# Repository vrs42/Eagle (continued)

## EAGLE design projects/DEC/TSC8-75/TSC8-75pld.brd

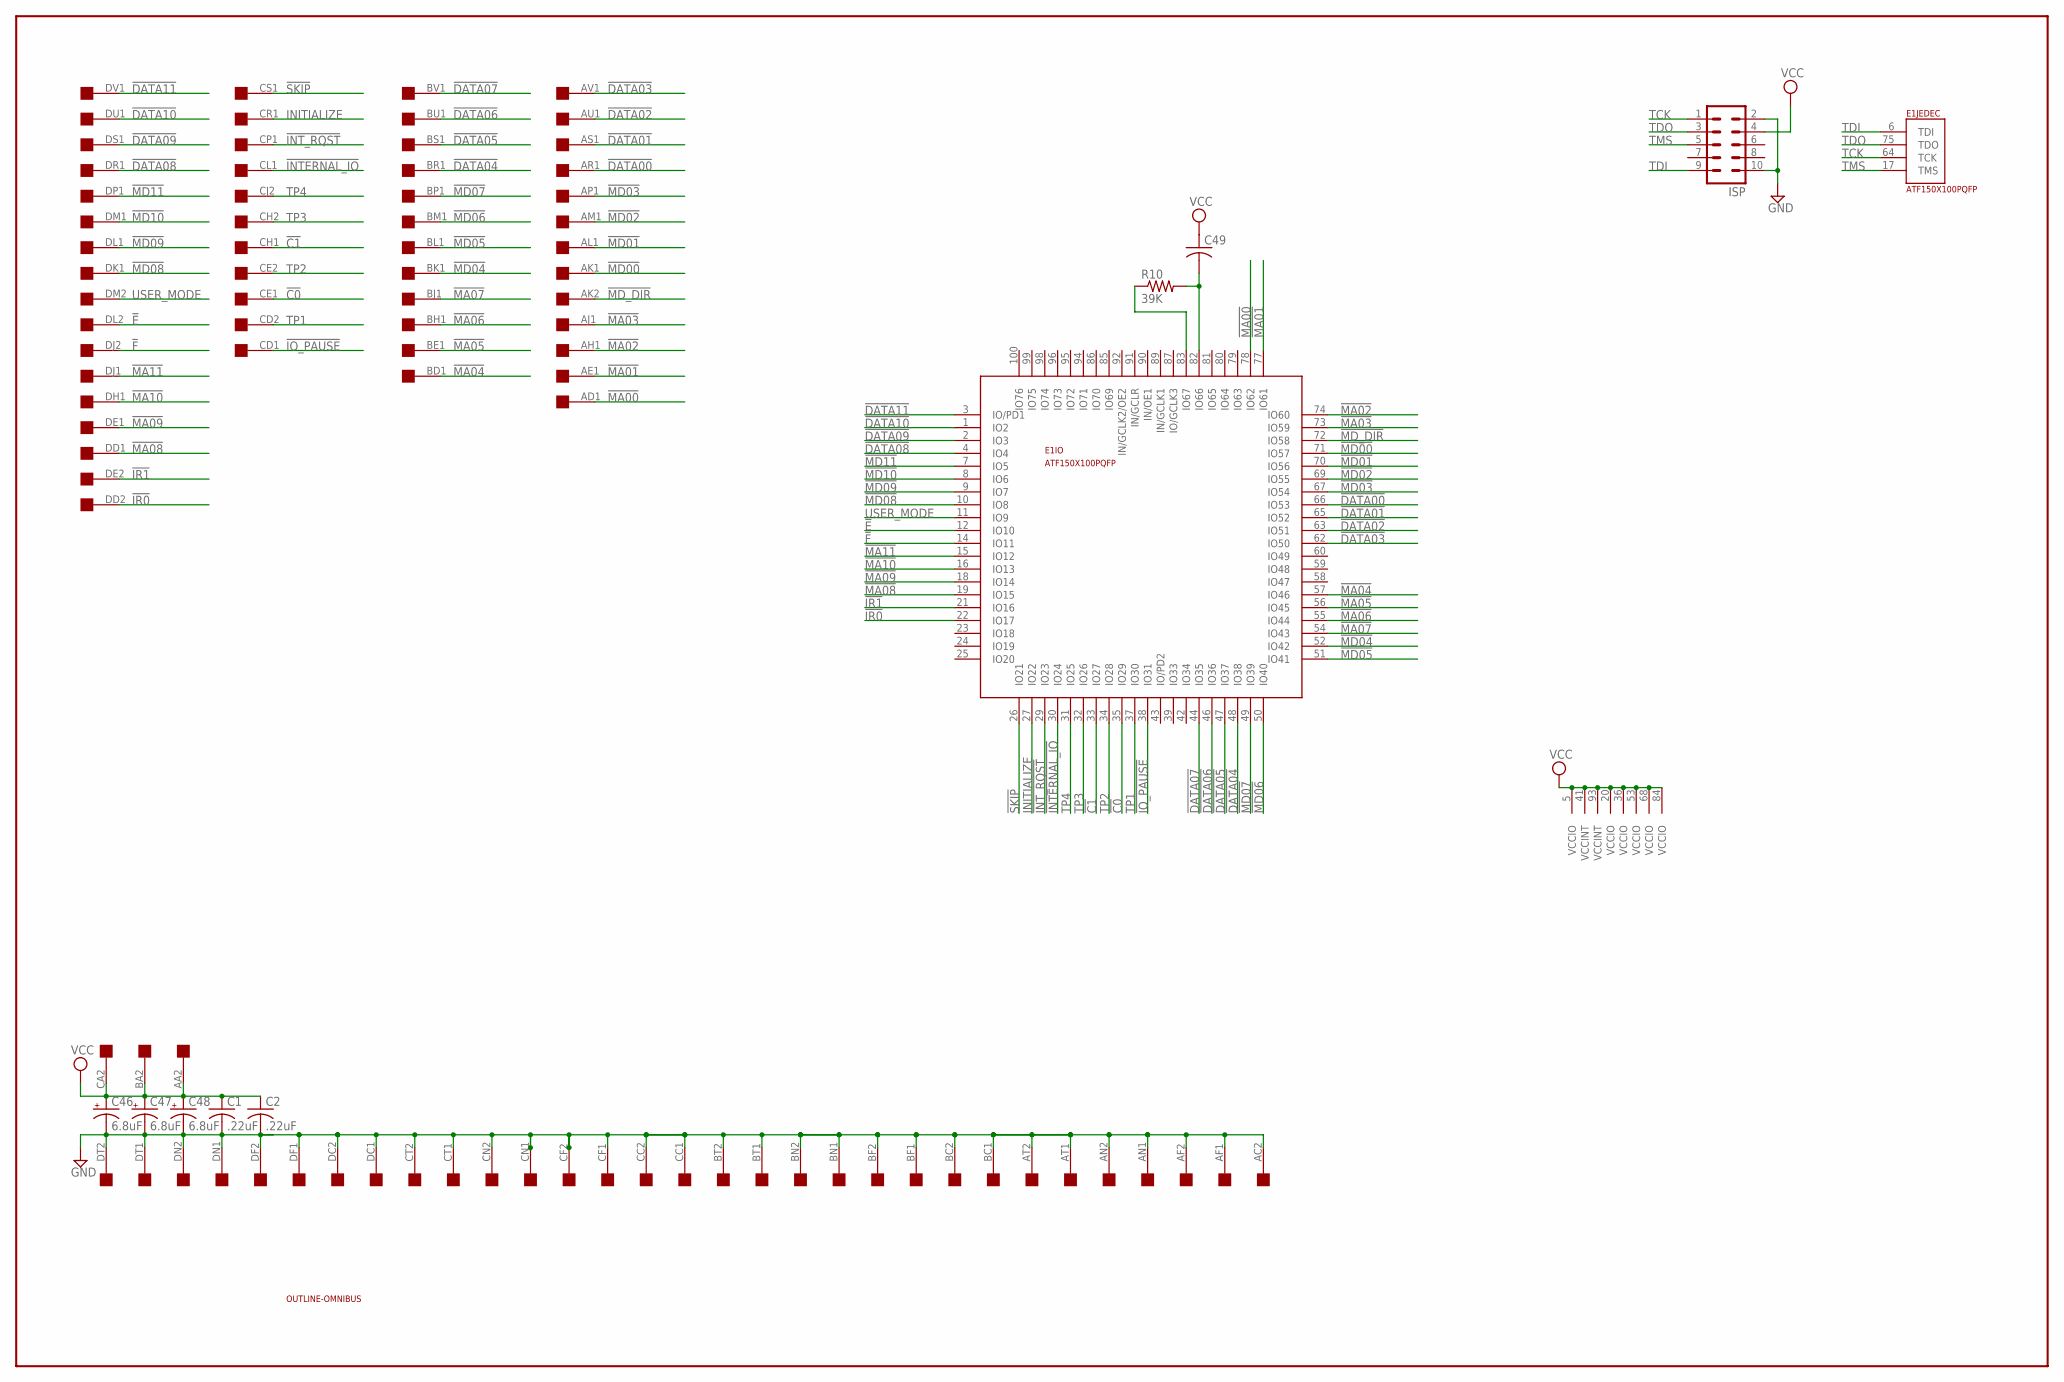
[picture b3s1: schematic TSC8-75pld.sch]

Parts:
C1, C2: .22uF; C050-025X075
C46, C47, C48: 6.8uF; E12-8
C49: C-US050-025X075; C050-025X075
E1: ATF150X100PQFP; PQFP-100
EDGE: QUAD; EDGE-CON8
ISP: ML10
R10: 39K; 0204/7
U$1: OUTLINE-OMNIBUS; OMNIBUS

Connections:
!C0: E1.35 (IO29), EDGE.CE1
!C1: E1.33 (IO27), EDGE.CH1
!DATA00: E1.66 (IO53), EDGE.AR1
!DATA01: E1.65 (IO52), EDGE.AS1
!DATA02: E1.63 (IO51), EDGE.AU1
!DATA03: E1.62 (IO50), EDGE.AV1
!DATA04: E1.48 (IO38), EDGE.BR1
!DATA05: E1.47 (IO37), EDGE.BS1
!DATA06: E1.46 (IO36), EDGE.BU1
!DATA07: E1.44 (IO35), EDGE.BV1
!DATA08: E1.4 (IO4), EDGE.DR1
!DATA09: E1.2 (IO3), EDGE.DS1
!DATA10: E1.1 (IO2), EDGE.DU1
!DATA11: E1.3 (IO/PD1), EDGE.DV1
!E: E1.12 (IO10), EDGE.DL2
!F: E1.14 (IO11), EDGE.DJ2
!INTERNAL_IO: E1.30 (IO24), EDGE.CL1
!INT_RQST: E1.29 (IO23), EDGE.CP1
!IO_PAUSE: E1.38 (IO31), EDGE.CD1
!IR0: E1.22 (IO17), EDGE.DD2
!IR1: E1.21 (IO16), EDGE.DE2
!MA00: E1.78 (IO62), EDGE.AD1
!MA01: E1.77 (IO61), EDGE.AE1
!MA02: E1.74 (IO60), EDGE.AH1
!MA03: E1.73 (IO59), EDGE.AJ1
!MA04: E1.57 (IO46), EDGE.BD1
!MA05: E1.56 (IO45), EDGE.BE1
!MA06: E1.55 (IO44), EDGE.BH1
!MA07: E1.54 (IO43), EDGE.BJ1
!MA08: E1.19 (IO15), EDGE.DD1
!MA09: E1.18 (IO14), EDGE.DE1
!MA10: E1.16 (IO13), EDGE.DH1
!MA11: E1.15 (IO12), EDGE.DJ1
!MD00: E1.71 (IO57), EDGE.AK1
!MD01: E1.70 (IO56), EDGE.AL1
!MD02: E1.69 (IO55), EDGE.AM1
!MD03: E1.67 (IO54), EDGE.AP1
!MD04: E1.52 (IO42), EDGE.BK1
!MD05: E1.51 (IO41), EDGE.BL1
!MD06: E1.50 (IO40), EDGE.BM1
!MD07: E1.49 (IO39), EDGE.BP1
!MD08: E1.10 (IO8), EDGE.DK1
!MD09: E1.9 (IO7), EDGE.DL1
!MD10: E1.8 (IO6), EDGE.DM1
!MD11: E1.7 (IO5), EDGE.DP1
!MD_DIR: E1.72 (IO58), EDGE.AK2
!SKIP: E1.26 (IO21), EDGE.CS1
GND: C1.2, C2.2, C46.-, C47.-, C48.-, E1.13 (GND), E1.28 (GND), E1.40 (GND), E1.45 (GND), E1.61 (GND), E1.76 (GND), E1.88 (GND), E1.97 (GND), EDGE.AC2, EDGE.AF1, EDGE.AF2, EDGE.AN1, EDGE.AN2, EDGE.AT1, EDGE.AT2, EDGE.BC1, EDGE.BC2, EDGE.BF1, EDGE.BF2, EDGE.BN1, EDGE.BN2, EDGE.BT1, EDGE.BT2, EDGE.CC1, EDGE.CC2, EDGE.CF1, EDGE.CF2, EDGE.CN1, EDGE.CN2, EDGE.CT1, EDGE.CT2, EDGE.DC1, EDGE.DC2, EDGE.DF1, EDGE.DF2, EDGE.DN1, EDGE.DN2, EDGE.DT1, EDGE.DT2, ISP.2, ISP.10
INITIALIZE: E1.27 (IO22), EDGE.CR1
unnamed: E1.83 (IO67), R10.1
unnamed: C49.2, E1.82 (IO66), R10.2
TCK: E1.64 (TCK), ISP.1
TDI: E1.6 (TDI), ISP.9
TDO: E1.75 (TDO), ISP.3
TMS: E1.17 (TMS), ISP.5
TP1: E1.37 (IO30), EDGE.CD2
TP2: E1.34 (IO28), EDGE.CE2
TP3: E1.32 (IO26), EDGE.CH2
TP4: E1.31 (IO25), EDGE.CJ2
USER_MODE: E1.11 (IO9), EDGE.DM2
VCC: C1.1, C2.1, C46.+, C47.+, C48.+, C49.1, E1.5 (VCCIO), E1.20 (VCCIO), E1.36 (VCCIO), E1.41 (VCCINT), E1.53 (VCCIO), E1.68 (VCCIO), E1.84 (VCCIO), E1.93 (VCCINT), EDGE.AA2, EDGE.BA2, EDGE.CA2, ISP.4

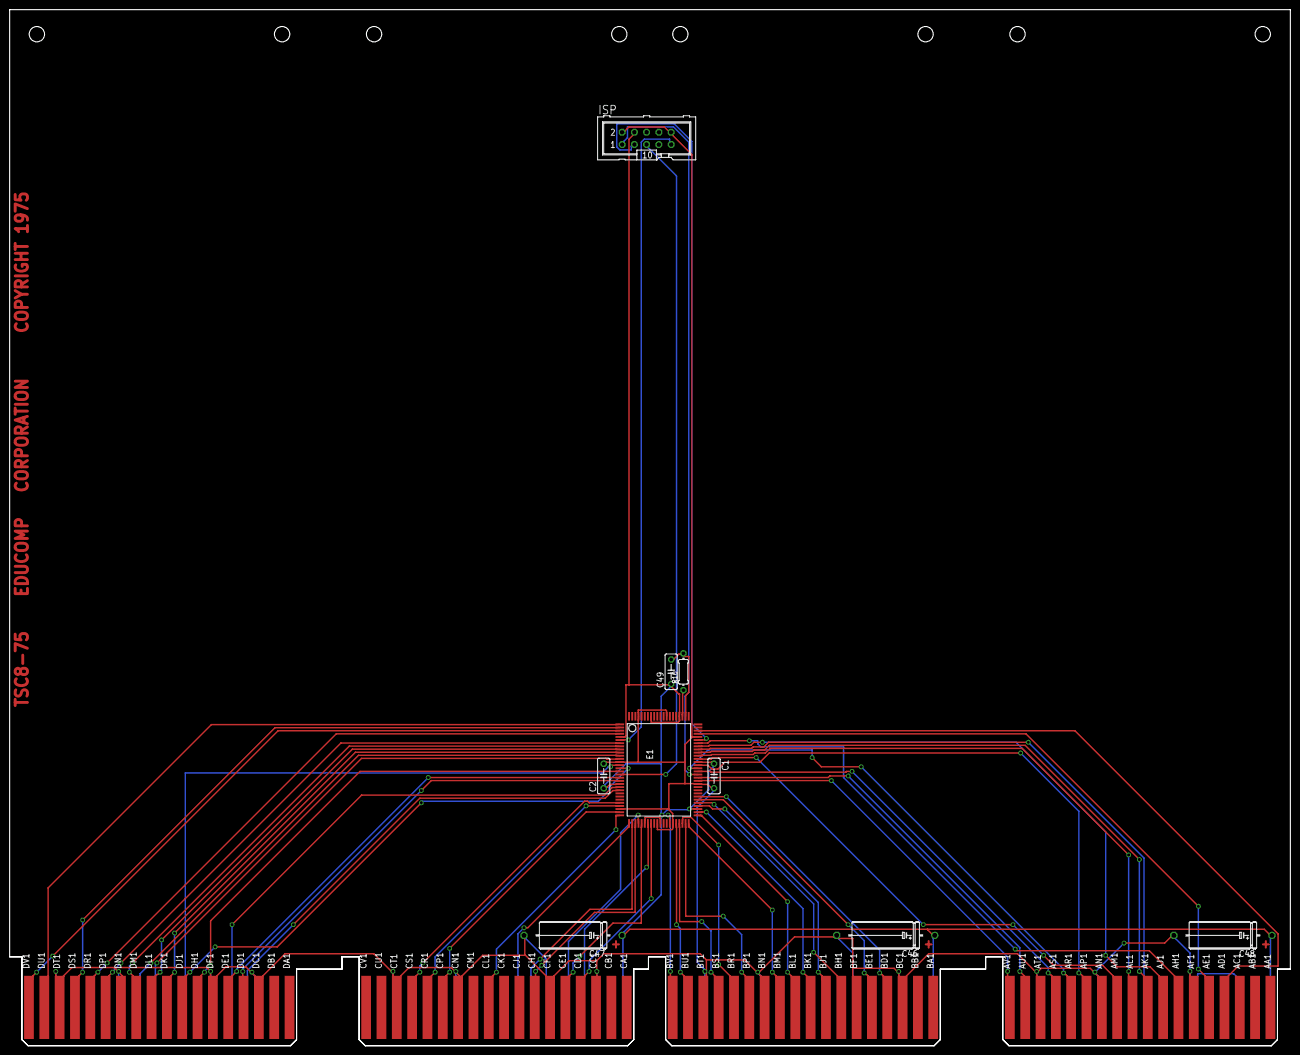
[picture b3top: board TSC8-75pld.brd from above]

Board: 4 copper layers, 265.3 x 214.6 mm, 11 parts (0 on the bottom side), 61 nets.

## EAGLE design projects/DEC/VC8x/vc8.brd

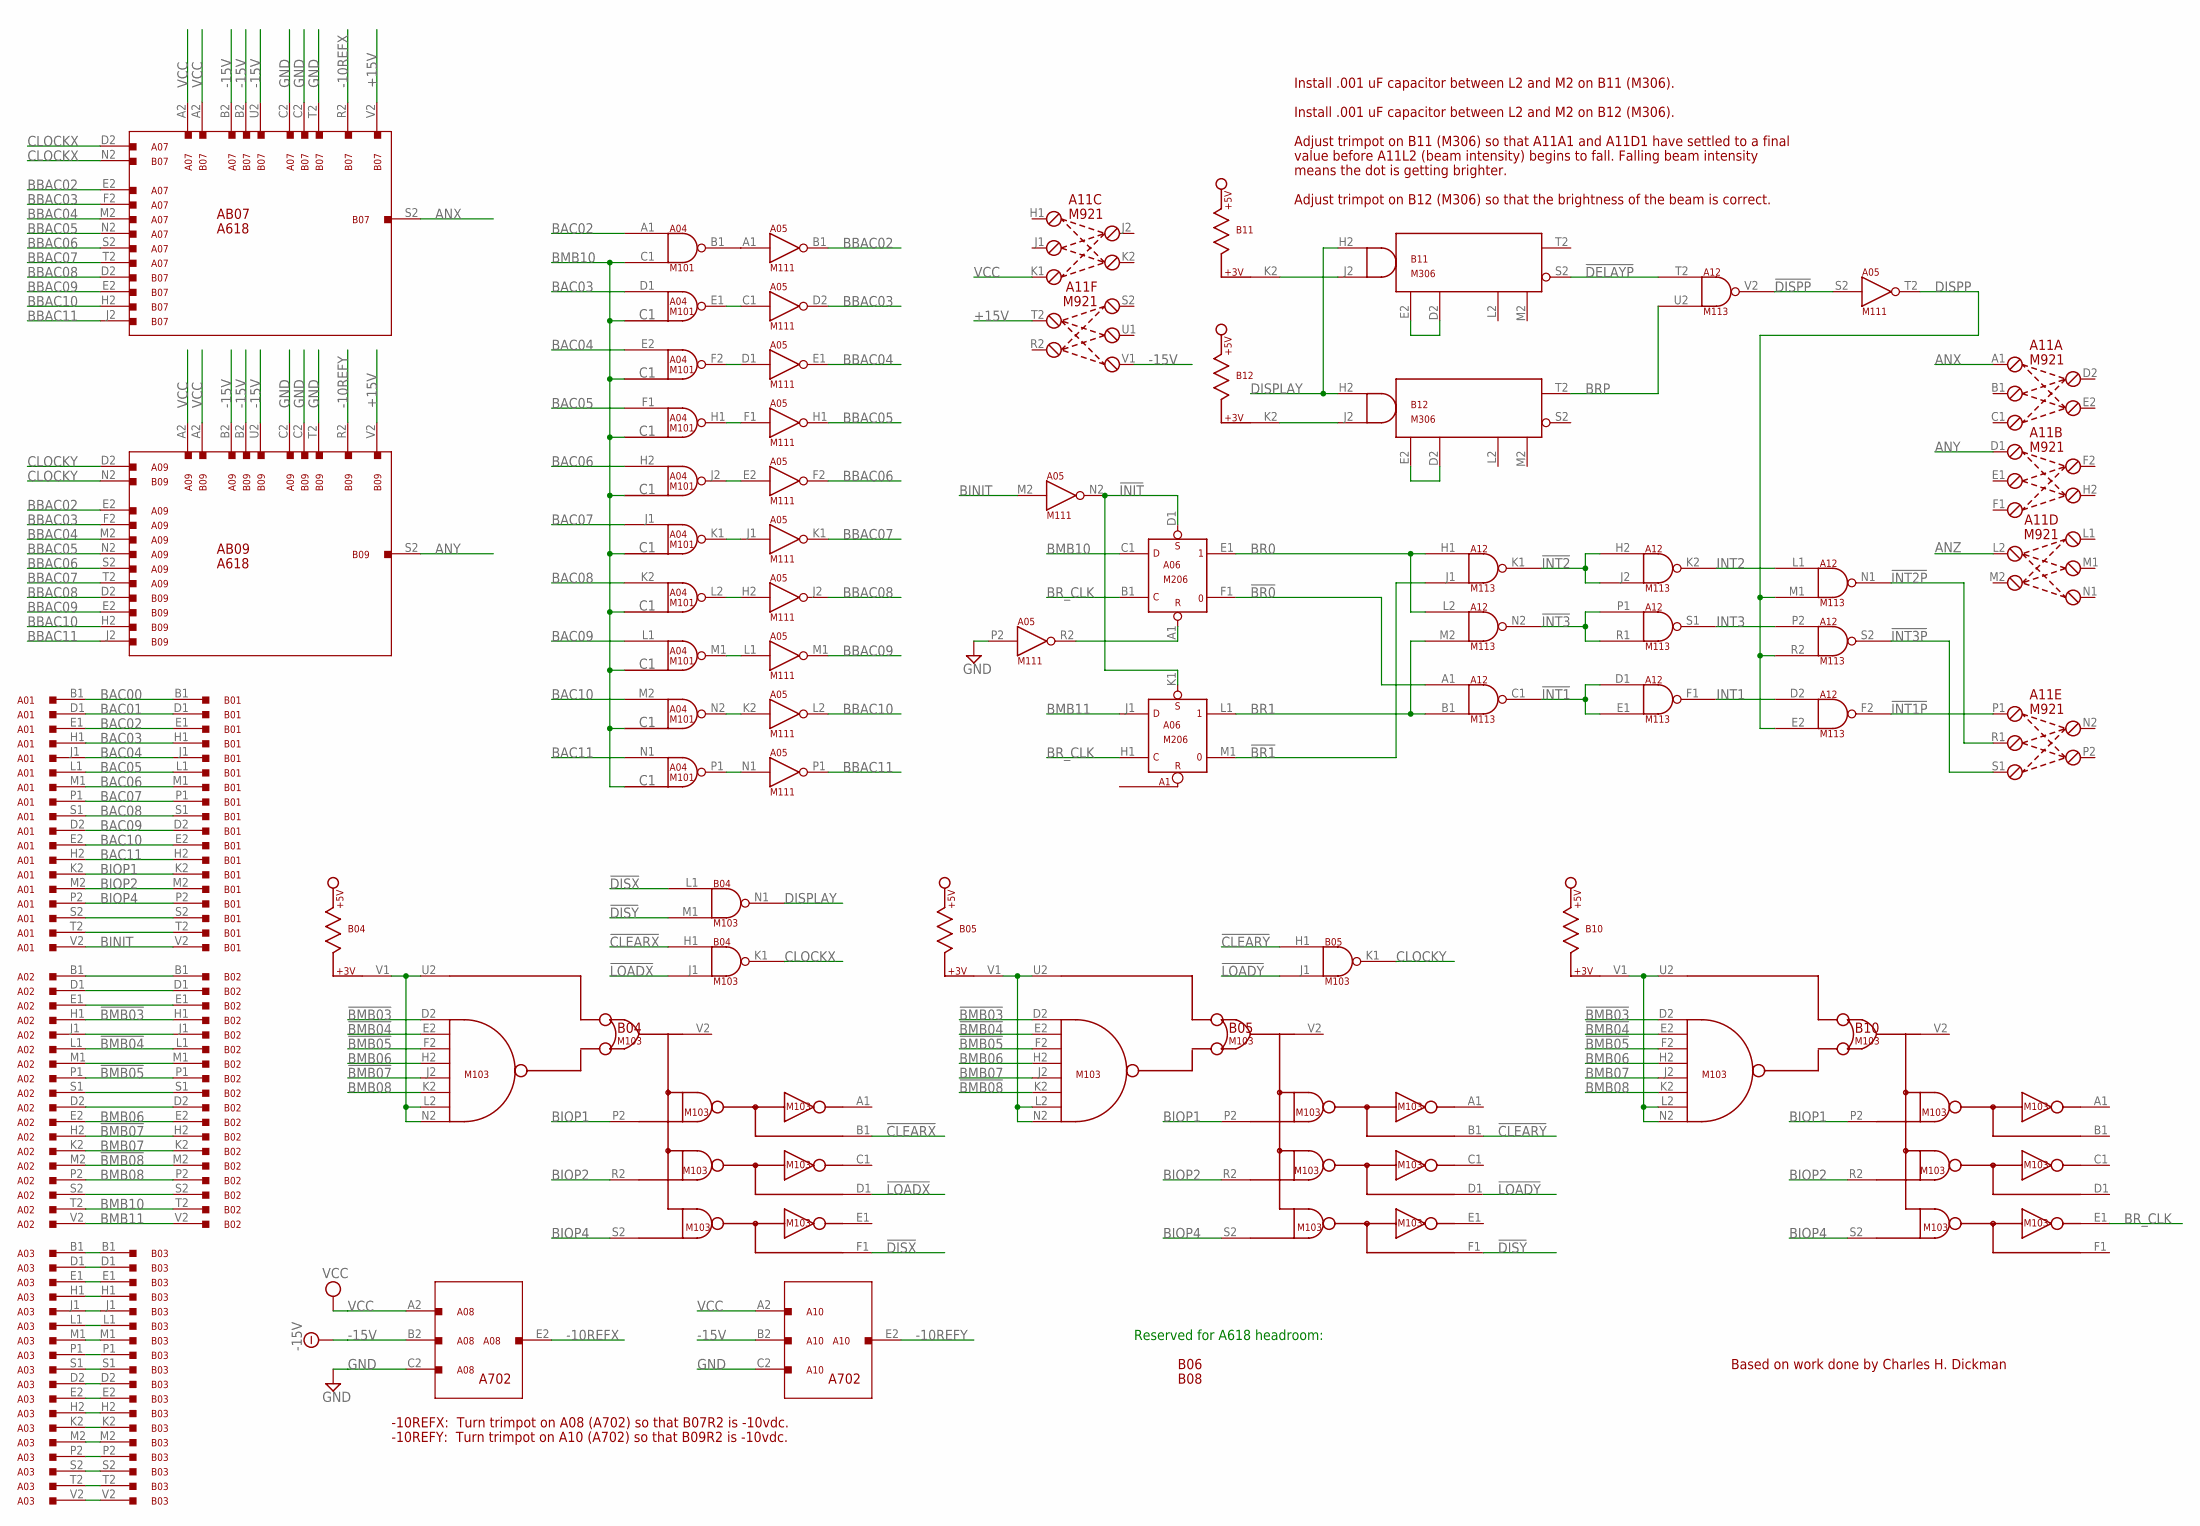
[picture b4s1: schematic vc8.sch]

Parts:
A01, A02, A03: M903; H807
A04: M101; H807
A05: M111; H807
A06: M206; H807
A07, A09: A618A; H807
A08, A10: A702; H807
A11: M921; H807
A12: M113; H807
B01, B02, B03: M903; H807
B04, B05, B10: M103; H807
B06, B08: EMPTY; H807
B07, B09: A618B; H807
B11, B12: M306; H807

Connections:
!BMB03: A02.H1, B02.H1, B04.D2, B05.D2, B10.D2
!BMB04: A02.L1, B02.L1, B04.E2, B05.E2, B10.E2
!BMB05: A02.P1, B02.P1, B04.F2, B05.F2, B10.F2
!BMB07: A02.H2, B02.H2, B04.J2
!BMB08: A02.M2, B02.M2, B05.K2
!BR0: A06.F1 (0), A12.A1 (IN1)
!BR1: A06.M1 (0), A12.J1 (IN2)
!CLEARX: B04.B1, B04.H1 (IN1)
!CLEARY: B05.B1, B05.H1 (IN1)
!DELAYP: A12.T2 (IN1), B11.S2 (S)
!DISPP: A05.S2 (IN), A12.V2 (OUT)
!DISX: B04.F1, B04.L1 (IN1)
!DISY: B04.M1 (IN2), B05.F1
!INIT: A05.N2 (OUT), A06.D1 (S), A06.K1 (S)
!INT1: A12.C1 (OUT), A12.D1 (IN1), A12.E1 (IN2)
!INT1P: A11.P1 (L1), A12.F2 (OUT)
!INT2: A12.H2 (IN1), A12.J2 (IN2), A12.K1 (OUT)
!INT2P: A11.R1 (L2), A12.N1 (OUT)
!INT3: A12.N2 (OUT), A12.P1 (IN1), A12.R1 (IN2)
!INT3P: A11.S1 (L3), A12.S2 (OUT)
!LOADX: B04.D1, B04.J1 (IN2)
!LOADY: B05.D1, B05.J1 (IN2)
+3VB04: B04.L2, B04.N2, B04.U2, B04.V1
+3VB05: B05.L2, B05.N2, B05.U2, B05.V1
+3VB10: B10.L2, B10.N2, B10.U2, B10.V1
+15V: A11.T2 (R1), B07.V2, B09.V2
-10REFX: A08.E2, B07.R2
-10REFY: A10.E2, B09.R2
-15V: A07.B2, A08.B2, A09.B2, A10.B2, A11.V1 (L3), B06.B2 (-15V), B07.B2, B07.U2, B08.B2 (-15V), B09.B2, B09.U2
ANX: A11.A1 (L1), B07.S2
ANY: A11.D1 (L1), B09.S2
ANZ: A11.L2 (R1)
BAC00: A01.B1, B01.B1
BAC01: A01.D1, B01.D1
BAC02: A01.E1, A04.A1 (IN1), B01.E1
BAC03: A01.H1, A04.D1 (IN), B01.H1
BAC04: A01.J1, A04.E2 (IN), B01.J1
BAC05: A01.L1, A04.F1 (IN), B01.L1
BAC06: A01.M1, A04.H2 (IN), B01.M1
BAC07: A01.P1, A04.J1 (IN), B01.P1
BAC08: A01.S1, A04.K2 (IN), B01.S1
BAC09: A01.D2, A04.L1 (IN), B01.D2
BAC10: A01.E2, A04.M2 (IN), B01.E2
BAC11: A01.H2, A04.N1 (IN), B01.H2
BBAC02: A05.B1 (OUT), A07.E2, A09.E2
BBAC03: A05.D2 (OUT), A07.F2, A09.F2
BBAC04: A05.E1 (OUT), A07.M2, A09.M2
BBAC05: A05.H1 (OUT), A07.N2, A09.N2
BBAC06: A05.F2 (OUT), A07.S2, A09.S2
BBAC07: A05.K1 (OUT), A07.T2, A09.T2
BBAC08: A05.J2 (OUT), B07.D2, B09.D2
BBAC09: A05.M1 (OUT), B07.E2, B09.E2
BBAC10: A05.L2 (OUT), B07.H2, B09.H2
BBAC11: A05.P1 (OUT), B07.J2, B09.J2
BINIT: A01.V2, A05.M2 (IN), B01.V2
BIOP1: A01.K2, B01.K2, B04.P2, B05.P2, B10.P2
BIOP2: A01.M2, B01.M2, B04.R2, B05.R2, B10.R2
BIOP4: A01.P2, B01.P2, B04.S2, B05.S2, B10.S2
BMB06: A02.E2, B02.E2, B04.H2, B05.H2, B10.H2
BMB07: A02.K2, B02.K2, B05.J2, B10.J2
BMB08: A02.P2, B02.P2, B04.K2, B10.K2
BMB10: A02.T2, A04.C1 (IN2), A06.C1 (D), B02.T2
BMB11: A02.V2, A06.J1 (D), B02.V2
BR0: A06.E1 (1), A12.H1 (IN1), A12.L2 (IN1)
BR1: A06.L1 (1), A12.B1 (IN2), A12.M2 (IN2)
BRP: A12.U2 (IN2), B12.T2 (T)
BR_CLK: A06.B1 (C), A06.H1 (C), B10.E1
CLOCKX: A07.D2, B04.K1 (OUT), B07.N2
CLOCKY: A09.D2, B05.K1 (OUT), B09.N2
DISPLAY: B04.N1 (OUT), B11.H2 (H), B12.H2 (H)
DISPP: A05.T2 (OUT), A12.E2 (IN2), A12.M1 (IN2), A12.R2 (IN2)
GND: A01.A1 (GND), A01.C1 (GND), A01.C2 (GND), A01.F1 (GND), A01.F2 (GND), A01.J2 (GND), A01.K1 (GND), A01.L2 (GND), A01.N1 (GND), A01.N2 (GND), A01.R1 (GND), A01.R2 (GND), A01.T1 (GND), A01.U2 (GND), A02.A1 (GND), A02.C1 (GND), A02.C2 (GND), A02.F1 (GND), A02.F2 (GND), A02.J2 (GND), A02.K1 (GND), A02.L2 (GND), A02.N1 (GND), A02.N2 (GND), A02.R1 (GND), A02.R2 (GND), A02.T1 (GND), A02.U2 (GND), A03.A1 (GND), A03.C1 (GND), A03.C2 (GND), A03.F1 (GND), A03.F2 (GND), A03.J2 (GND), A03.K1 (GND), A03.L2 (GND), A03.N1 (GND), A03.N2 (GND), A03.R1 (GND), A03.R2 (GND), A03.T1 (GND), A03.U2 (GND), A04.C2 (GND), A04.T1 (GND), A05.C2 (GND), A05.P2 (IN), A05.T1 (GND), A06.C2 (GND), A06.T1 (GND), A07.C2, A08.C2, A09.C2, A10.C2, A12.C2 (GND), A12.T1 (GND), B01.A1 (GND), B01.C1 (GND), B01.C2 (GND), B01.F1 (GND), B01.F2 (GND), B01.J2 (GND), B01.K1 (GND), B01.L2 (GND), B01.N1 (GND), B01.N2 (GND), B01.R1 (GND), B01.R2 (GND), B01.T1 (GND), B01.U2 (GND), B02.A1 (GND), B02.C1 (GND), B02.C2 (GND), B02.F1 (GND), B02.F2 (GND), B02.J2 (GND), B02.K1 (GND), B02.L2 (GND), B02.N1 (GND), B02.N2 (GND), B02.R1 (GND), B02.R2 (GND), B02.T1 (GND), B02.U2 (GND), B03.A1 (GND), B03.C1 (GND), B03.C2 (GND), B03.F1 (GND), B03.F2 (GND), B03.J2 (GND), B03.K1 (GND), B03.L2 (GND), B03.N1 (GND), B03.N2 (GND), B03.R1 (GND), B03.R2 (GND), B03.T1 (GND), B03.U2 (GND), B04.C2 (GND), B04.T1 (GND), B05.C2 (GND), B05.T1 (GND), B06.C2 (GND), B07.C2, B07.T2, B08.C2 (GND), B09.C2, B09.T2, B10.C2 (GND), B10.T1 (GND), B11.C2 (GND), B12.C2 (GND)
INT1: A12.D2 (IN1), A12.F1 (OUT)
INT2: A12.K2 (OUT), A12.L1 (IN1)
INT3: A12.P2 (IN1), A12.S1 (OUT)
unnamed: A05.R2 (OUT), A06.A1 (R)
unnamed: B11.J2 (J), B11.K2
unnamed: B12.J2 (J), B12.K2
unnamed: B11.D2 (D), B11.E2 (E)
unnamed: B12.D2 (D), B12.E2 (E)
unnamed: A04.B1 (OUT), A05.A1 (IN)
unnamed: A04.E1 (OUT), A05.C1 (IN)
unnamed: A04.F2 (OUT), A05.D1 (IN)
unnamed: A04.H1 (OUT), A05.F1 (IN)
unnamed: A04.J2 (OUT), A05.E2 (IN)
unnamed: A04.P1 (OUT), A05.N1 (IN)
unnamed: A04.N2 (OUT), A05.K2 (IN)
unnamed: A04.M1 (OUT), A05.L1 (IN)
unnamed: A04.L2 (OUT), A05.H2 (IN)
unnamed: A04.K1 (OUT), A05.J1 (IN)
unnamed: A03.B1, B03.B1
unnamed: A03.D1, B03.D1
unnamed: A03.E1, B03.E1
unnamed: A03.H1, B03.H1
unnamed: A03.J1, B03.J1
unnamed: A03.L1, B03.L1
unnamed: A03.M1, B03.M1
unnamed: A03.P1, B03.P1
unnamed: A03.S1, B03.S1
unnamed: A03.D2, B03.D2
unnamed: A03.E2, B03.E2
unnamed: A03.H2, B03.H2
unnamed: A03.K2, B03.K2
unnamed: A03.M2, B03.M2
unnamed: A03.P2, B03.P2
unnamed: A03.S2, B03.S2
unnamed: A03.T2, B03.T2
unnamed: A03.V2, B03.V2
unnamed: A02.D2, B02.D2
unnamed: A02.S1, B02.S1
unnamed: A02.J1, B02.J1
unnamed: A02.M1, B02.M1
unnamed: A02.S2, B02.S2
unnamed: A02.B1, B02.B1
unnamed: A02.D1, B02.D1
unnamed: A02.E1, B02.E1
unnamed: A01.T2, B01.T2
unnamed: A01.S2, B01.S2
VCC: A04.A2 (VCC), A05.A2 (VCC), A06.A2 (VCC), A07.A2, A08.A2, A09.A2, A10.A2, A11.K1 (L3), A12.A2 (VCC), B04.A2 (VCC), B05.A2 (VCC), B06.A2 (VCC), B07.A2, B08.A2 (VCC), B09.A2, B10.A2 (VCC), B11.A2 (VCC), B12.A2 (VCC)

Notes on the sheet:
Reserved for A618 headroom:
A702
AB07
A618
AB09
Install .001 uF capacitor between L2 and M2 on B11 (M306).
Install .001 uF capacitor between L2 and M2 on B12 (M306).
-10REFX: Turn trimpot on A08 (A702) so that B07R2 is -10vdc.
-10REFY: Turn trimpot on A10 (A702) so that B09R2 is -10vdc.
Adjust trimpot on B11 (M306) so that A11A1 and A11D1 have settled to a final
value before A11L2 (beam intensity) begins to fall. Falling beam intensity
means the dot is getting brighter.
Adjust trimpot on B12 (M306) so that the brightness of the beam is correct.
Based on work done by Charles H. Dickman

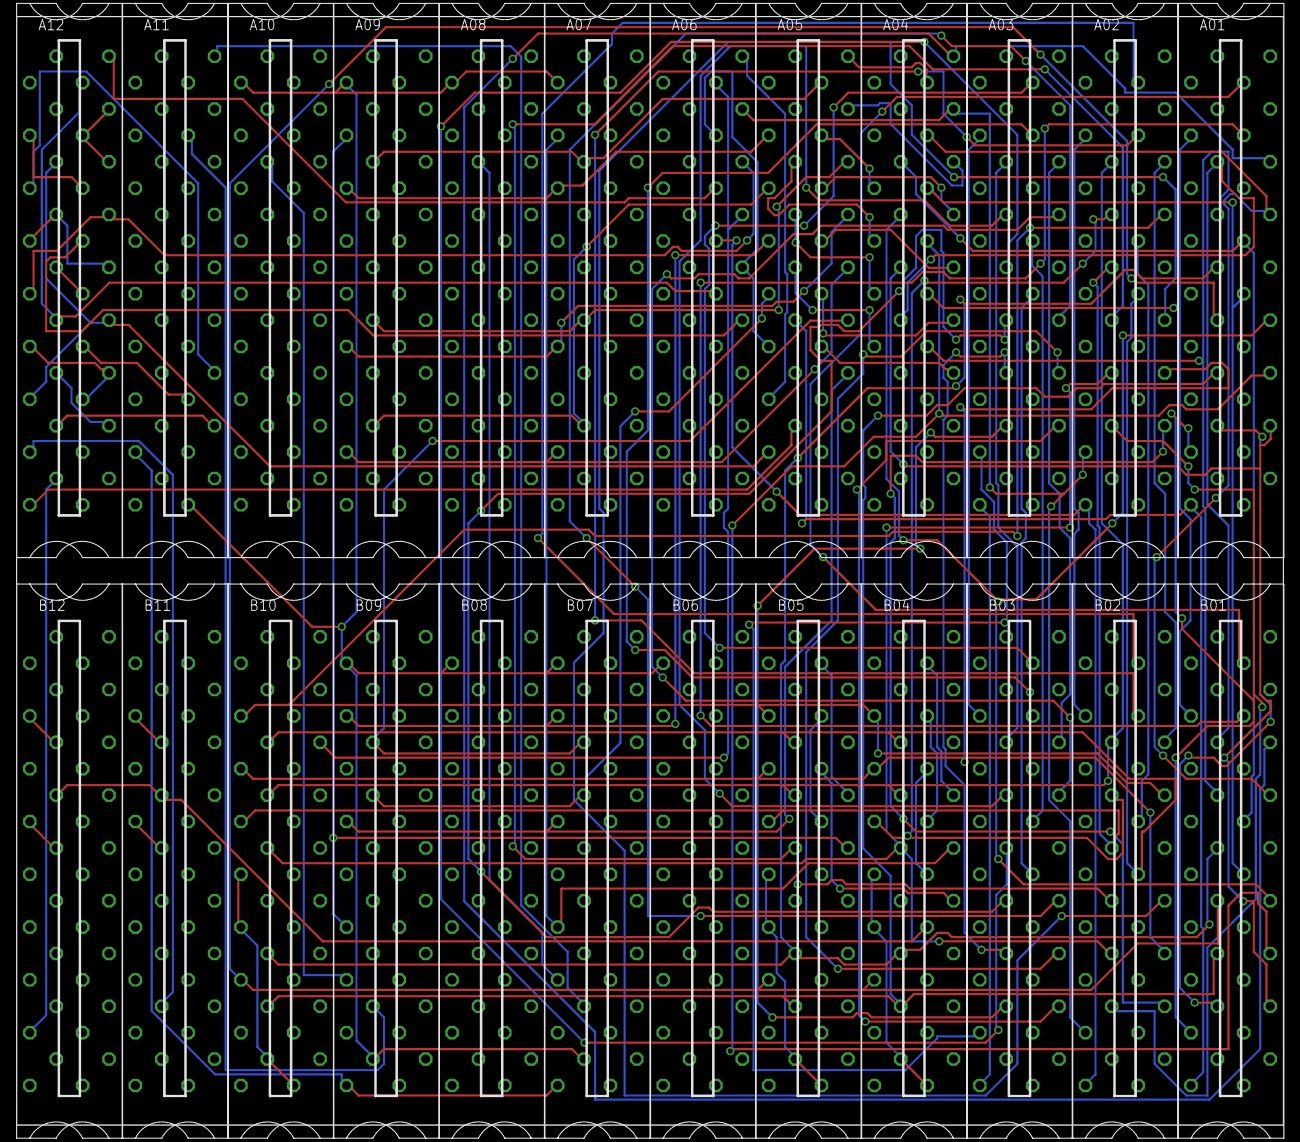
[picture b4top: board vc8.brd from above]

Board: 4 copper layers, 152.4 x 133.3 mm, 24 parts (0 on the bottom side), 118 nets.

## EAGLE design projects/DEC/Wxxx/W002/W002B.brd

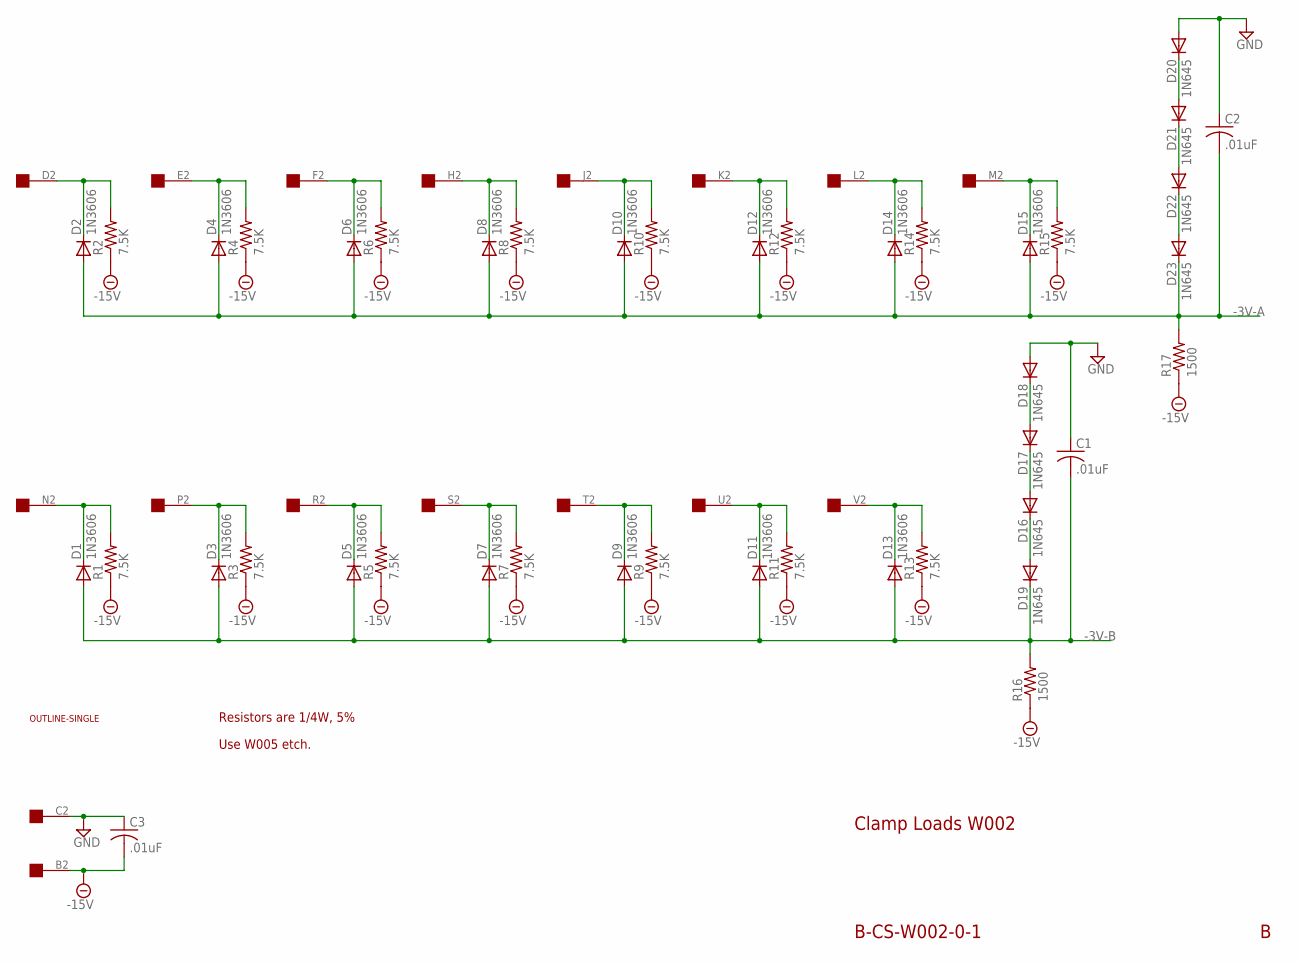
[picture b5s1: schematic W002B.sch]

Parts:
C1, C2, C3: .01uF; C050-025X075
D1, D2, D3, D4, D5, D6, D7, D8, D9, D10, D11, D12, D13, D14, D15: 1N3606; DO35-10
D16, D17, D18, D19, D20, D21, D22, D23: 1N645; DO35-10
R1, R2, R3, R4, R5, R6, R7, R8, R9, R10, R11, R12, R13, R14, R15: 7.5K; 0207/10
R16, R17: 1500; 0207/10
U$1: OUTLINE-SINGLE; SINGLE
U$2: EDGE-1; EDGE-CON1

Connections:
-3V-A: C2.2, D2.A, D4.A, D6.A, D8.A, D10.A, D12.A, D14.A, D15.A, D23.C, R17.2
-3V-B: C1.2, D1.A, D3.A, D5.A, D7.A, D9.A, D11.A, D13.A, D19.C, R16.2
-15V: C3.2, R1.1, R2.1, R3.1, R4.1, R5.1, R6.1, R7.1, R8.1, R9.1, R10.1, R11.1, R12.1, R13.1, R14.1, R15.1, R16.1, R17.1, U$2.B2
GND: C1.1, C2.1, C3.1, D18.A, D20.A, U$2.C2
unnamed: D22.C, D23.A
unnamed: D2.C, R2.2, U$2.D2
unnamed: D4.C, R4.2, U$2.E2
unnamed: D1.C, R1.2, U$2.N2
unnamed: D3.C, R3.2, U$2.P2
unnamed: D5.C, R5.2, U$2.R2
unnamed: D6.C, R6.2, U$2.F2
unnamed: D7.C, R7.2, U$2.S2
unnamed: D8.C, R8.2, U$2.H2
unnamed: D9.C, R9.2, U$2.T2
unnamed: D10.C, R10.2, U$2.J2
unnamed: D11.C, R11.2, U$2.U2
unnamed: D12.C, R12.2, U$2.K2
unnamed: D13.C, R13.2, U$2.V2
unnamed: D14.C, R14.2, U$2.L2
unnamed: D15.C, R15.2, U$2.M2
unnamed: D17.A, D18.C
unnamed: D16.A, D17.C
unnamed: D16.C, D19.A
unnamed: D20.C, D21.A
unnamed: D21.C, D22.A

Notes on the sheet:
Clamp Loads W002
B-CS-W002-0-1
Resistors are 1/4W, 5%
Use W005 etch.

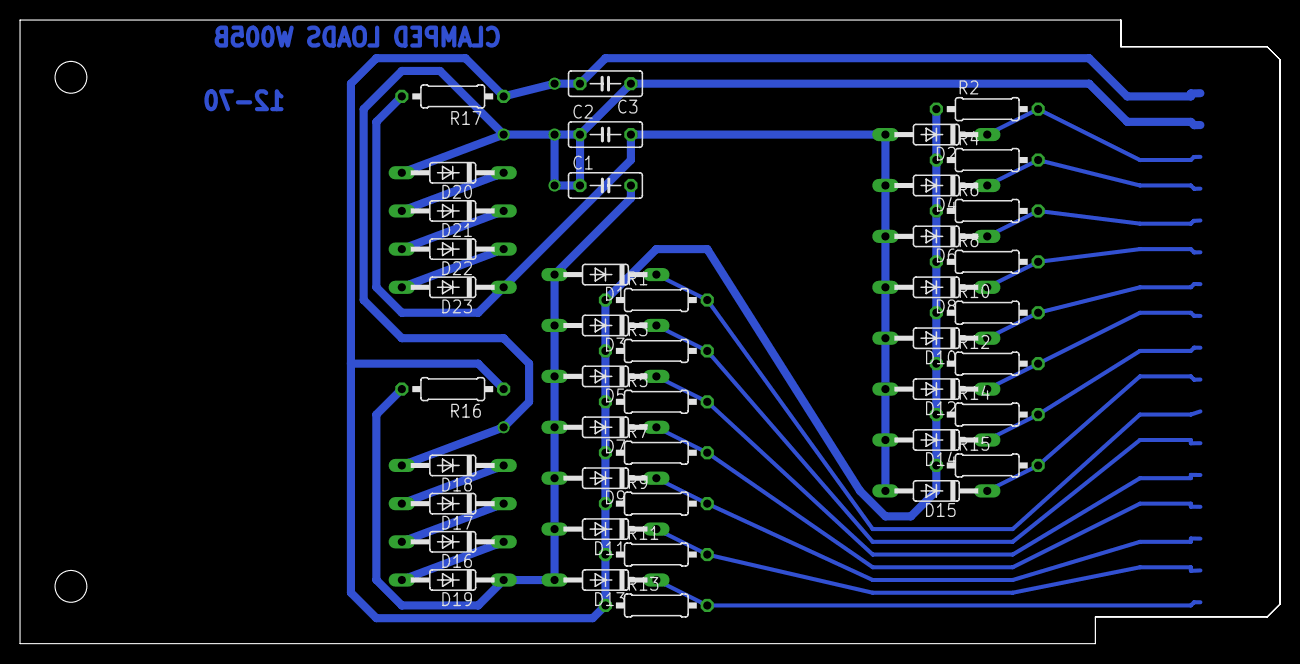
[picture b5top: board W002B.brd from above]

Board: 2 copper layers, 125.7 x 62.2 mm, 45 parts (0 on the bottom side), 25 nets.

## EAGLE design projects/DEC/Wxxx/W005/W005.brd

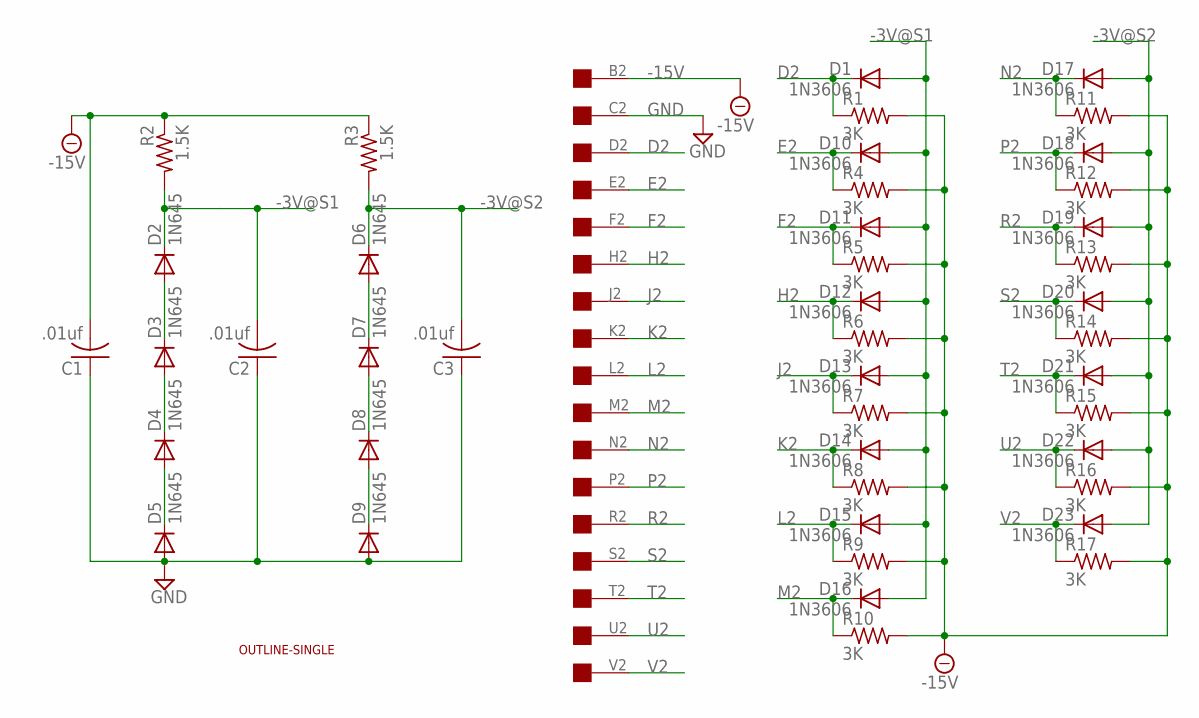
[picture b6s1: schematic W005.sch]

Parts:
C1, C2, C3: .01uf; C050-025X075
D1, D10, D11, D12, D13, D14, D15, D16, D17, D18, D19, D20, D21, D22, D23: 1N3606; DO35-10
D2, D3, D4, D5, D6, D7, D8, D9: 1N645; DO35-10
R1, R4, R5, R6, R7, R8, R9, R10, R11, R12, R13, R14, R15, R16, R17: 3K; 0207/10
R2, R3: 1.5K; 0207/10
U$1: EDGE-1; EDGE-CON1
U$2: OUTLINE-SINGLE; SINGLE

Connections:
-3V@S1: C2.2, D1.A, D2.C, D10.A, D11.A, D12.A, D13.A, D14.A, D15.A, D16.A, R2.2
-3V@S2: C3.2, D6.C, D17.A, D18.A, D19.A, D20.A, D21.A, D22.A, D23.A, R3.2
-15V: C1.2, R1.2, R2.1, R3.1, R4.2, R5.2, R6.2, R7.2, R8.2, R9.2, R10.2, R11.2, R12.2, R13.2, R14.2, R15.2, R16.2, R17.2, U$1.B2
D2: D1.C, R1.1, U$1.D2
E2: D10.C, R4.1, U$1.E2
F2: D11.C, R5.1, U$1.F2
GND: C1.1, C2.1, C3.1, D5.A, D9.A, U$1.C2
H2: D12.C, R6.1, U$1.H2
J2: D13.C, R7.1, U$1.J2
K2: D14.C, R8.1, U$1.K2
L2: D15.C, R9.1, U$1.L2
M2: D16.C, R10.1, U$1.M2
N2: D17.C, R11.1, U$1.N2
unnamed: D2.A, D3.C
unnamed: D3.A, D4.C
unnamed: D4.A, D5.C
unnamed: D8.A, D9.C
unnamed: D7.A, D8.C
unnamed: D6.A, D7.C
P2: D18.C, R12.1, U$1.P2
R2: D19.C, R13.1, U$1.R2
S2: D20.C, R14.1, U$1.S2
T2: D21.C, R15.1, U$1.T2
U2: D22.C, R16.1, U$1.U2
V2: D23.C, R17.1, U$1.V2

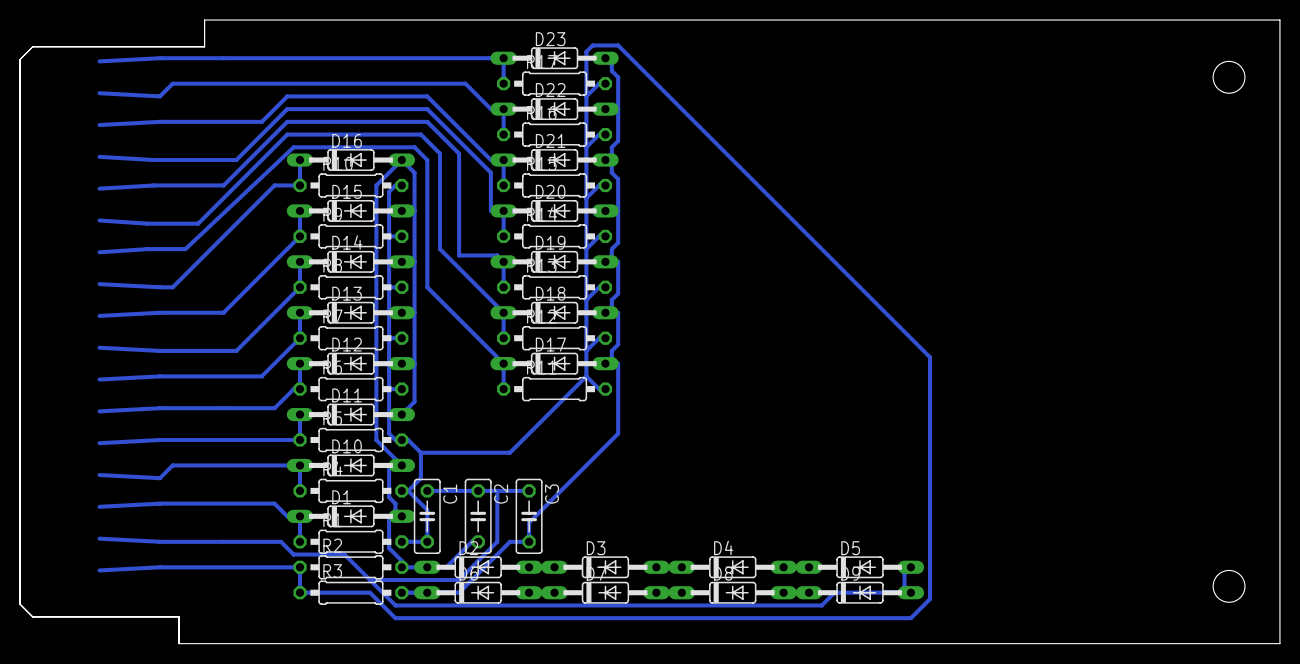
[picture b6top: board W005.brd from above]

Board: 2 copper layers, 125.7 x 62.2 mm, 45 parts (0 on the bottom side), 25 nets.
